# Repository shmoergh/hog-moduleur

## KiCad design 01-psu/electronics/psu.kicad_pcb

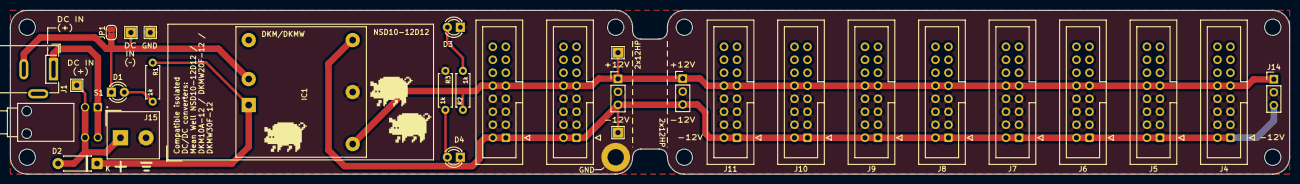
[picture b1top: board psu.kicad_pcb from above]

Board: 2 copper layers, 250.0 x 32.0 mm, 38 parts (0 on the bottom side), 10 nets.

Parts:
D1, D3, D4: LED; LED_D3.0mm
D2: 1N4001; D_DO-41_SOD81_P7.62mm_Horizontal
H1, H2, H3, H4, H5, H6, H7: MountingHole; MountingHole_3.2mm_M3_DIN965
H9: MountingHole_Pad; MountingHole_3.2mm_M3_DIN965_Pad
IC1: ISOLATED_DC-DC_CONV; Converter_DCDC_MeanWell_NSD10_DKMW_THT
J1: Barrel_Jack_Switch; BarrelJack_Wuerth_6941xx301002
J2, J3, J4, J5, J6, J7, J8, J9, J10, J11: Conn_02x08_Odd_Even; IDC-Header_2x08_P2.54mm_Vertical
J12, J13, J14: Conn_01x03; PinHeader_1x03_P2.54mm_Vertical
J15: Screw_Terminal_01x02; Altech_AK100_1x02_P5.00mm
JP1: Jumper_2_Open; SolderJumper-2_P1.3mm_Bridged2Bar_RoundedPad1.0x1.5mm
R1, R2, R3: 1k; R_Axial_DIN0207_L6.3mm_D2.5mm_P7.62mm_Horizontal
S1: PB400EEQR1BLK; SW_PB400EEQR1BLK
TP1, TP2, TP3, TP4, TP5: TestPoint; TestPoint_THTPad_2.0x2.0mm_Drill1.0mm

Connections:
+12V: IC1.3 (+OUT), J2.9, J2.10, J3.9, J3.10, J4.9, J4.10, J5.9, J5.10, J6.9, J6.10, J7.9, J7.10, J8.9, J8.10, J9.9, J9.10, J10.9, J10.10, J11.9, J11.10, J12.1, J13.1, J14.1, R2.1, TP4.1
-12V: D4.1 (K), IC1.5 (-OUT), J2.1, J2.2, J3.1, J3.2, J4.1, J4.2, J5.1, J5.2, J6.1, J6.2, J7.1, J7.2, J8.1, J8.2, J9.1, J9.2, J10.1, J10.2, J11.1, J11.2, J12.3, J13.3, J14.3, TP5.1
DC_IN_+: D2.1 (K), IC1.1 (+IN), R1.1
DC_IN_-: D1.1 (K), IC1.2 (-IN), J1.2, JP1.1 (A), TP2.1
GND: D3.1 (K), H9.1, IC1.4 (Common), J2.3, J2.4, J2.5, J2.6, J2.7, J2.8, J3.3, J3.4, J3.5, J3.6, J3.7, J3.8, J4.3, J4.4, J4.5, J4.6, J4.7, J4.8, J5.3, J5.4, J5.5, J5.6, J5.7, J5.8, J6.3, J6.4, J6.5, J6.6, J6.7, J6.8, J7.3, J7.4, J7.5, J7.6, J7.7, J7.8, J8.3, J8.4, J8.5, J8.6, J8.7, J8.8, J9.3, J9.4, J9.5, J9.6, J9.7, J9.8, J10.3, J10.4, J10.5, J10.6, J10.7, J10.8, J11.3, J11.4, J11.5, J11.6, J11.7, J11.8, J12.2, J13.2, J14.2, J15.2, JP1.2 (B), R3.1, TP3.1
unnamed: D1.2 (A), R1.2
unnamed: D2.2 (A), J15.1, S1.2, S1.4, TP1.1
unnamed: D3.2 (A), R2.2
unnamed: D4.2 (A), R3.2
unnamed: J1.1, S1.1, S1.3

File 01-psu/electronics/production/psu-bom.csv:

"Reference","Qty","Value","Part No.","Part URL","Vendor"
"D1,D3,D4","3","LED","604-WP710A10ID","https://mou.sr/45uKc0N","Mouser"
"D2","1","1N4001","637-1N4001 ","https://mou.sr/3DfEJyK","Mouser"
"IC1","1","ISOLATED_DC-DC_CONV","709-NSD10-12D12 ","https://mou.sr/3ZpECrS","Mouser"
"J1","1","Barrel_Jack_Switch","710-694106301002 ","https://mou.sr/4a9ckVQ","Mouser"
"J2,J3,J4,J5,J6,J7,J8,J9,J10,J11","10","Conn_02x08_Odd_Even","737-BHR-16-VUA","https://mou.sr/4jUmWfT","Mouser"
"J15","1","Screw_Terminal_01x02","737-EBBA-02-C-SS-BU ","https://mou.sr/4jUbpxn","Mouser"
"R1,R2,R3","3","1k","303-MF0W4FF1001A10 ","https://mou.sr/3ZzOD6G","Mouser"
"S1","1","PB400EEQR1BLK","612-PB400EEQR1BLK ","https://mou.sr/3TDv9tV","Mouser"

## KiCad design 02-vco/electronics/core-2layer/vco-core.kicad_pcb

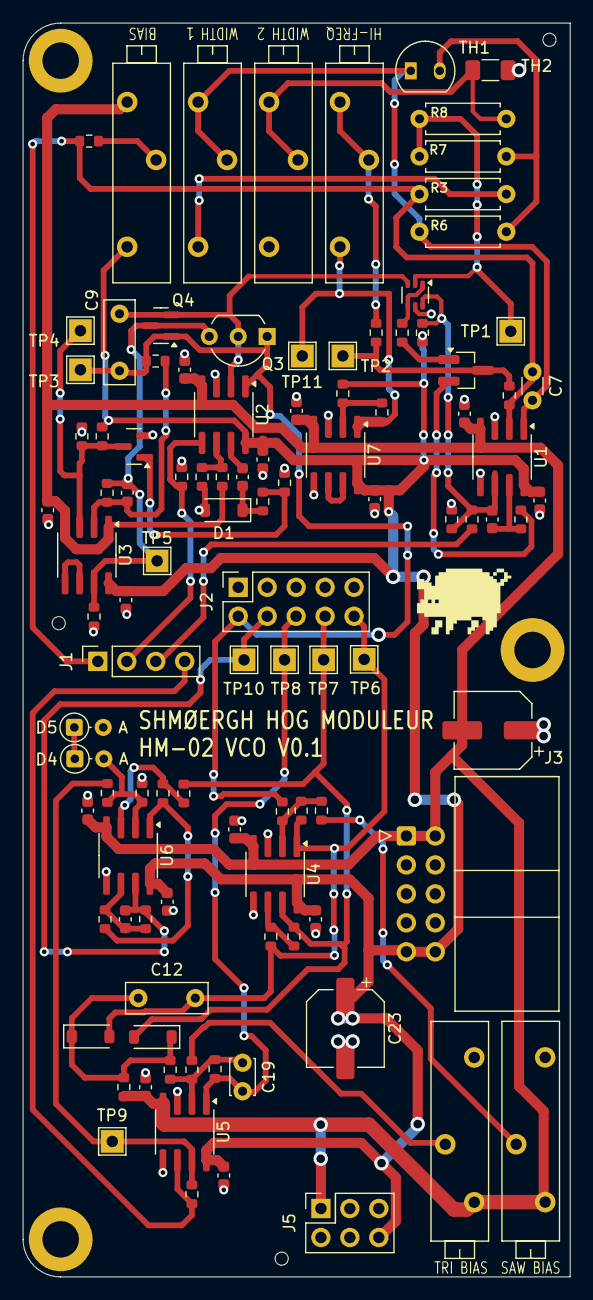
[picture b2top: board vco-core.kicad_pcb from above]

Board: 2 copper layers, 48.0 x 110.0 mm, 107 parts (0 on the bottom side), 49 nets.

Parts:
C1, C2, C3, C4, C5, C6, C13, C14, C15, C16, C17, C18, C21, C22: 100n; C_0603_1608Metric
C7: 100p-1n; C_Disc_D3.0mm_W1.6mm_P2.50mm
C8: 100p; C_0603_1608Metric
C9: 2.2nF (foil); C_Rect_L7.2mm_W2.5mm_P5.00mm_FKS2_FKP2_MKS2_MKP2
C10: 22p; C_0603_1608Metric
C11: 47p; C_0603_1608Metric
C12: 10p-100p; C_Rect_L7.0mm_W2.5mm_P5.00mm
C19: 22p; C_Disc_D3.0mm_W2.0mm_P2.50mm
C20: 33p; C_0603_1608Metric
C23, C24: 100u; CP_Elec_6.3x7.7
D1, D2, D3: 1N4148; D_SOD-123
D4, D5: 5.1V; D_DO-34_SOD68_P2.54mm_Vertical_AnodeUp
H1, H2, H3: MountingHole; MountingHole_3.2mm_M3_DIN965_Pad
J1: Conn_01x04; PinSocket_1x04_P2.54mm_Vertical
J2: Conn_02x05_Odd_Even; PinSocket_2x05_P2.54mm_Vertical
J3: Conn_02x05_Odd_Even; IDC-Header_2x05_P2.54mm_Horizontal
J5: Conn_02x03_Odd_Even; PinSocket_2x03_P2.54mm_Vertical
Q1: BC847BS; SOT-363_SC-70-6
Q2: MMBT3906; SOT-23_Handsoldering
Q3: J111; TO-92_Inline_Wide
Q4: MMBFJ111; SOT-23
Q5: MMBT5551; SOT-23
R1, R5, R15, R18, R21, R25, R27, R28, R29, R30, R37, R38, R40: 100k; R_0603_1608Metric
R2, R17: 150k; R_0603_1608Metric
R3, R6, R7, R8: See t.comp. table; R_Axial_DIN0207_L6.3mm_D2.5mm_P7.62mm_Horizontal
R4, R10, R13: 1M; R_0603_1608Metric
R9, R11: 1.5k; R_0603_1608Metric
R12: 510; R_0603_1608Metric
R14: 10k; R_0603_1608Metric
R16: 22k; R_0603_1608Metric
R19: 330k; R_0603_1608Metric
R20, R33: 2.2k; R_0603_1608Metric
R22, R32: 47k; R_0603_1608Metric
R23, R24: 15k; R_0603_1608Metric
R26: 27k; R_0603_1608Metric
R31, R34: 220k; R_0603_1608Metric
R35: 2.2M; R_0603_1608Metric
R36, R39: 240k; R_0603_1608Metric
RV_SAW_BIAS1: 10k; Potentiometer_Bourns_3006P_Horizontal
RV_TRI_BIAS1: 100k; Potentiometer_Bourns_3006P_Horizontal
R_BIAS1: 100k (prec); Potentiometer_Bourns_3006P_Horizontal
R_HIFREQ1: 2k (prec); Potentiometer_Bourns_3006P_Horizontal
R_WIDTH1, R_WIDTH2: See t.comp. table; Potentiometer_Bourns_3006P_Horizontal
TH1: See t.comp. table; TO-92-2
TH2: PTS120602B100RP100; R_1206_3216Metric_Pad1.30x1.75mm_HandSolder
TP1: -18mV/V; TestPoint_THTPad_2.0x2.0mm_Drill1.0mm
TP2: HiFreq; TestPoint_THTPad_2.0x2.0mm_Drill1.0mm
TP3: RAW_SAW; TestPoint_THTPad_2.0x2.0mm_Drill1.0mm
TP4: VCOVREF; TestPoint_THTPad_2.0x2.0mm_Drill1.0mm
TP5: Reset OUT; TestPoint_THTPad_2.0x2.0mm_Drill1.0mm
TP6: SAWInv; TestPoint_THTPad_2.0x2.0mm_Drill1.0mm
TP7: SAW; TestPoint_THTPad_2.0x2.0mm_Drill1.0mm
TP8: TRI; TestPoint_THTPad_2.0x2.0mm_Drill1.0mm
TP9: PW; TestPoint_THTPad_2.0x2.0mm_Drill1.0mm
TP10: SQR; TestPoint_THTPad_2.0x2.0mm_Drill1.0mm
TP11: -5V; TestPoint_THTPad_2.0x2.0mm_Drill1.0mm
U1, U2, U4, U5, U6, U7: TL072; SOIC-8_3.9x4.9mm_P1.27mm
U3: LM311; SOIC-8_3.9x4.9mm_P1.27mm

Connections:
+12V: C1.1, C3.1, C5.1, C13.1, C15.1, C17.1, C21.1, C23.1, J3.9, J3.10, J5.6, R10.1, R17.2, R39.1, R_BIAS1.1, U1.8 (V+), U2.8 (V+), U3.8 (V+), U4.8 (V+), U5.8 (V+), U6.8 (V+), U7.8 (V+)
-5V: R40.2, R_HIFREQ1.1, TP11.1, U7.1
-12V: C2.2, C4.2, C6.2, C14.2, C16.2, C18.2, C22.2, C24.2, J3.1, J3.2, J5.1, R15.2, R25.2, RV_SAW_BIAS1.3, RV_TRI_BIAS1.3, R_BIAS1.3, U1.4 (V-), U2.4 (V-), U3.1 (GND), U3.4 (V-), U4.4 (V-), U5.4 (V-), U6.4 (V-), U7.4 (V-)
/Raw oscillator/HI_FREQ_COMP: Q2.3 (C), R2.2, R12.1, TP2.1
/Raw oscillator/I_REF: C8.1, Q1.6 (C1), R4.2, R5.2, R10.2, U1.6 (-)
CV: C7.1, J1.1, R1.2, R2.1, R3.1, U1.2 (-)
FM: J1.3, R4.1
GND: C1.2, C2.1, C3.2, C4.1, C5.2, C6.1, C13.2, C14.1, C15.2, C16.1, C17.2, C18.1, C21.2, C22.1, C23.2, C24.1, D1.2 (A), D5.2 (A), J2.1, J2.3, J2.5, J2.7, J2.9, J3.3, J3.4, J3.5, J3.6, J3.7, J3.8, J5.2, J5.3, J5.4, J5.5, Q1.5 (B2), Q5.2 (E), R5.1, R13.2, R14.1, R18.1, R20.2, R22.2, R34.2, RV_SAW_BIAS1.1, RV_TRI_BIAS1.1, R_WIDTH2.1, TH2.2, U1.3 (+), U1.5 (+), U2.3 (+), U4.3 (+), U4.5 (+), U5.3 (+), U5.5 (+), U6.5 (+), U7.3 (+), U7.5 (+)
HARD_SYNC: J1.2, R13.1, U2.5 (+)
unnamed: C7.2, R6.1, R_WIDTH1.2, R_WIDTH1.3, TH1.1, U1.1
unnamed: C8.2, R9.1, U1.7
unnamed: C11.1, U2.7
unnamed: C11.2, D1.1 (K), R21.1
unnamed: C12.1, D2.1 (K), D3.1 (K), R25.1, R27.2
unnamed: D4.2 (A), R32.1, R34.1, U6.2 (-)
unnamed: D4.1 (K), D5.1 (K)
unnamed: Q1.2 (B1), R7.2, R8.1, TP1.1
unnamed: Q1.1 (E1), Q1.4 (E2), R11.1
unnamed: C9.1, Q1.3 (C2), Q3.2 (S), Q4.2 (S), U2.2 (-)
unnamed: Q2.2 (B), R9.2
unnamed: Q2.1 (E), R11.2
unnamed: C10.2, Q3.3 (G), Q4.3 (G), R19.2, R20.1, TP5.1, U3.7
unnamed: Q5.1 (B), R21.2, R22.1
unnamed: Q5.3 (C), R17.1, R18.2, TP4.1, U3.3 (-)
unnamed: R1.1, R_BIAS1.2
unnamed: R3.2, R_WIDTH1.1
unnamed: R6.2, R7.1, TH1.2
unnamed: R8.2, R_WIDTH2.2, R_WIDTH2.3, TH2.1
unnamed: R12.2, R_HIFREQ1.2, R_HIFREQ1.3
unnamed: R24.2, RV_SAW_BIAS1.2
unnamed: R28.2, RV_TRI_BIAS1.2
unnamed: R32.2, R37.2, TP9.1, U5.7
unnamed: R35.1, R36.2, U6.1
unnamed: R14.2, R15.1, U2.6 (-)
unnamed: C10.1, R16.2, R19.1, U3.2 (+)
unnamed: U3.5 (BAL), U3.6 (STRB)
unnamed: R23.1, R24.1, R26.2, U4.2 (-)
unnamed: R29.1, R30.2, U4.6 (-)
unnamed: C19.2, R27.1, R28.1, R31.2, U5.2 (-)
unnamed: R33.1, R35.2, U6.3 (+)
unnamed: C20.1, R36.1, R38.2, U6.6 (-)
unnamed: R39.2, R40.1, U7.2 (-)
unnamed: U7.6 (-), U7.7
RAW_SAW: C9.2, J2.2, Q3.1 (D), Q4.1 (D), R16.1, R23.2, TP3.1, U2.1
SAW: D2.2 (A), J2.8, R30.1, R33.2, TP7.1, U4.7
SAW_INV: C12.2, D3.2 (A), J2.10, R26.1, R29.2, TP6.1, U4.1
SQR: C20.2, J2.4, R38.1, TP10.1, U6.7
SQR_SHAPE: J1.4, R37.1, U5.6 (-)
TRI: C19.1, J2.6, R31.1, TP8.1, U5.1

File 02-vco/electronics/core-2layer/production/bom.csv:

Designator,Footprint,Quantity,Value,LCSC Part #
"_3, _2, ",,3,,
"C1, C13, C14, C15, C16, C17, C18, C2, C21, C22, C3, C4, C5, C6",0603,14,100n,C14663
C10,0603,1,22p,C1653
C11,0603,1,47p,C1671
C20,0603,1,33p,C1663
"C23, C24",CP_Elec_6.3x7.7,2,100u,C2836437
C8,0603,1,100p,C14858
"D1, D2, D3",D_SOD-123,3,1N4148,C81598
J1,PinSocket_1x04_P2.54mm_Vertical,1,Conn_01x04,
J2,PinSocket_2x05_P2.54mm_Vertical,1,Conn_02x05_Odd_Even,
J3,IDC-Header_2x05_P2.54mm_Horizontal,1,Conn_02x05_Odd_Even,
J5,PinSocket_2x03_P2.54mm_Vertical,1,Conn_02x03_Odd_Even,
Q1,SOT-363_SC-70-6,1,BC847BS,C5380687
Q2,SOT-23_Handsoldering,1,MMBT3906,C7420354
Q4,SOT-23,1,MMBFJ111,C274688
Q5,SOT-23,1,MMBT5551,C2145
"R1, R15, R18, R21, R25, R27, R28, R29, R30, R37, R38, R40, R5",0603,13,100k,C25803
"R10, R13, R4",0603,3,1M,C22935
"R11, R9",0603,2,1.5k,C22843
R12,0603,1,510,C23193
R14,0603,1,10k,C25804
R16,0603,1,22k,C31850
"R17, R2",0603,2,150k,C22807
R19,0603,1,330k,C23137
"R20, R33",0603,2,2.2k,C4190
"R22, R32",0603,2,47k,C25819
"R23, R24",0603,2,15k,C22809
R26,0603,1,27k,C22967
"R31, R34",0603,2,220k,C22961
R35,0603,1,2.2M,C22938
R36,0603,1,240k,C4197
R39,0603,1,240k,C2907016
RV_SAW_BIAS1,Potentiometer_Bourns_3006P_Horizontal,1,10k,
RV_TRI_BIAS1,Potentiometer_Bourns_3006P_Horizontal,1,100k,
"U1, U2, U4, U5, U6, U7",SOIC-8_3.9x4.9mm_P1.27mm,6,TL072,C6961
U3,SOIC-8_3.9x4.9mm_P1.27mm,1,LM311,C12597

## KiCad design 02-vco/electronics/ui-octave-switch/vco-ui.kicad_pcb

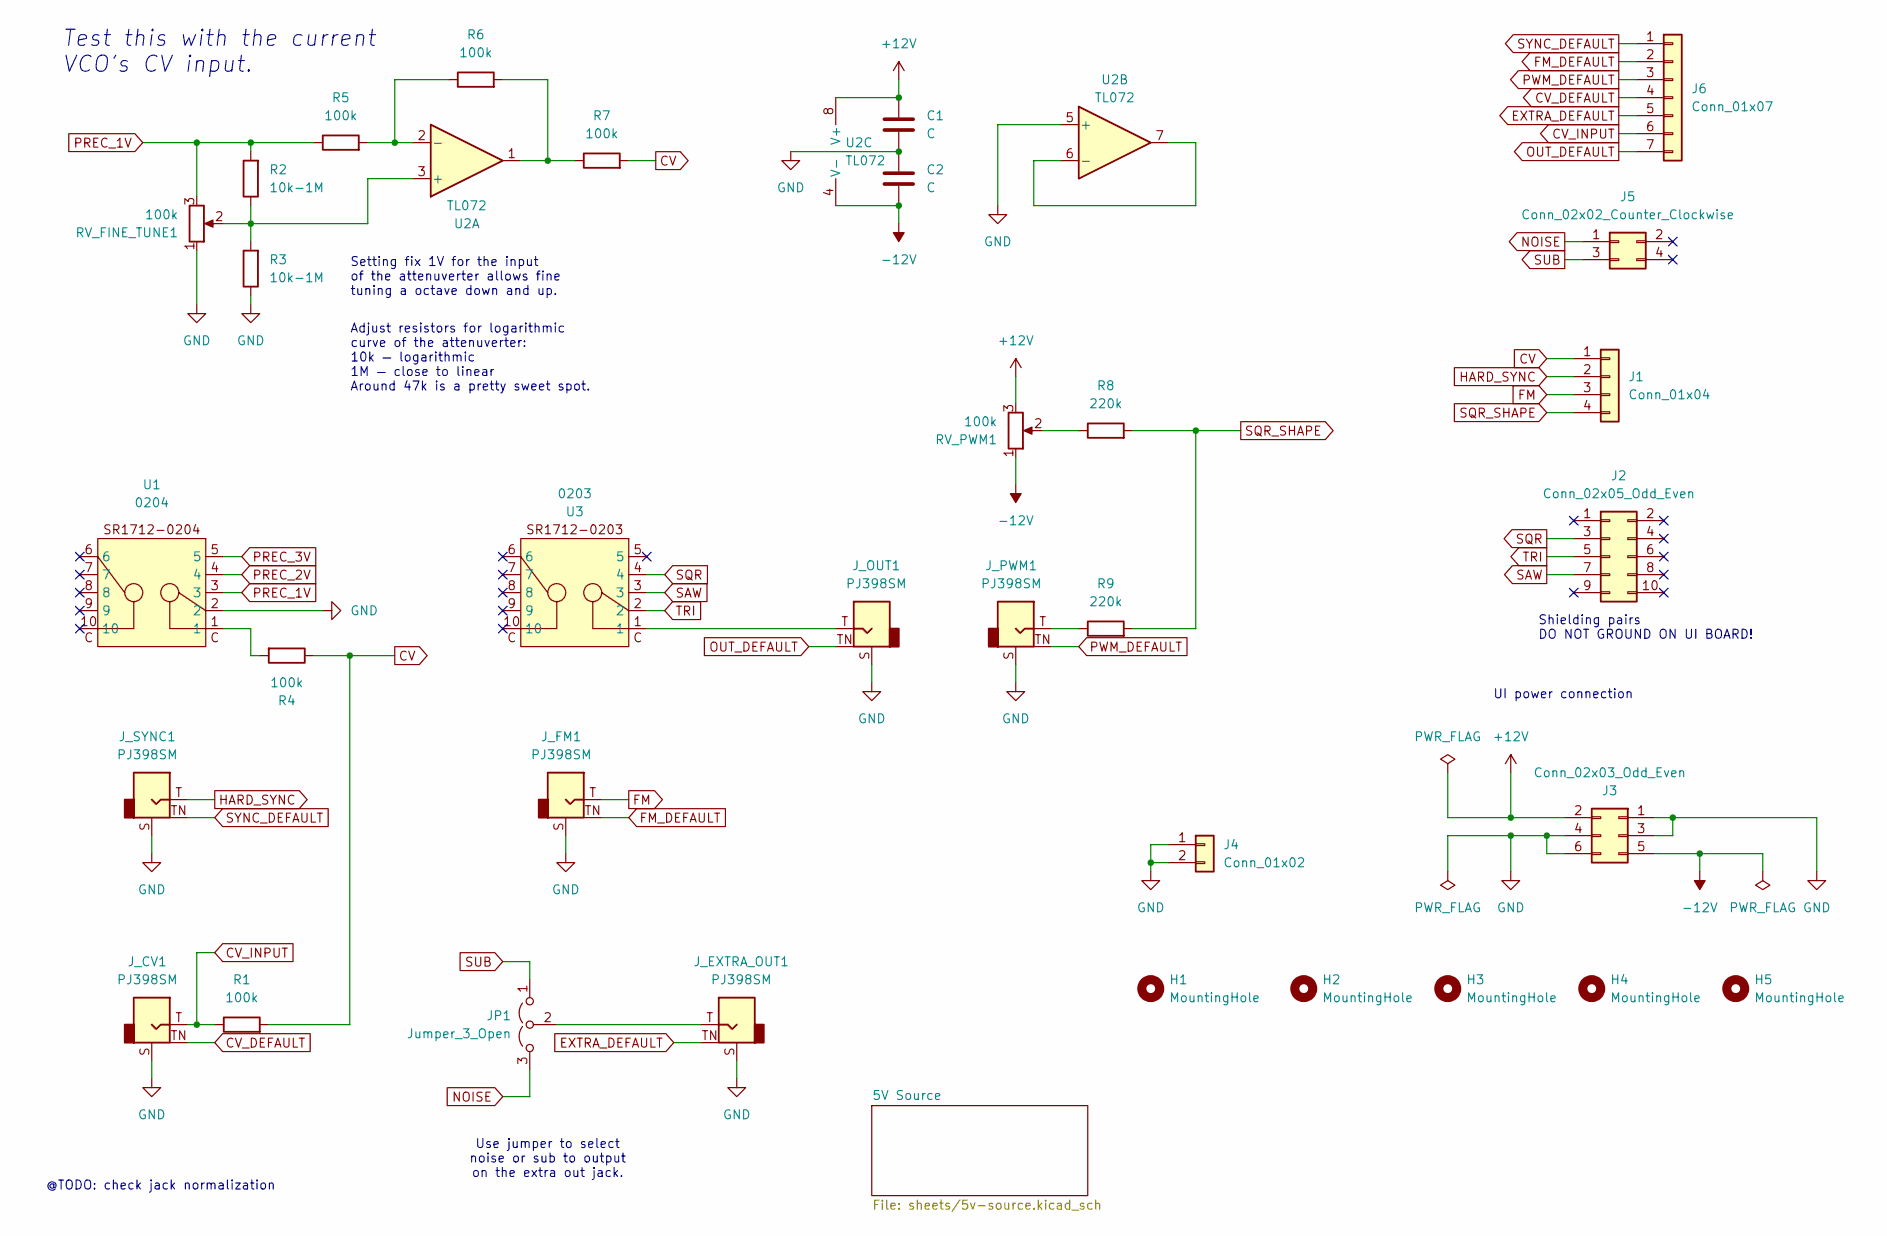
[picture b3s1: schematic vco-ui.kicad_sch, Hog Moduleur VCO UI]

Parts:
C1, C2: C; C_Disc_D5.0mm_W2.5mm_P2.50mm
H1, H2, H3, H4, H5: MountingHole; MountingHole_3.2mm_M3_DIN965_Pad
J1: Conn_01x04; PinSocket_1x04_P2.54mm_Vertical; Part no. 200-SSW10401TMS
J2: Conn_02x05_Odd_Even; PinSocket_2x05_P2.54mm_Vertical; Part no. 200-SSW10501TD
J3: Conn_02x03_Odd_Even; PinSocket_2x03_P2.54mm_Vertical; Part no. 200-SSW10301TD
J4: Conn_01x02; PinSocket_1x02_P2.54mm_Vertical; Part no. 200-SSW10201TS
J5: Conn_02x02_Counter_Clockwise; PinSocket_2x02_P2.54mm_Vertical; Part no. 200-SSW10206TD
J6: Conn_01x07; PinSocket_1x07_P2.54mm_Vertical; Part no. 200-SSW10601TS
JP1: Jumper_3_Open; PinHeader_1x03_P2.54mm_Horizontal; Part no. 200-HTSW10308TSRA
J_CV1: PJ398SM; Jack_3.5mm_QingPu_WQP-PJ398SM_Vertical_CircularHoles; Part no. PJ398SM
J_EXTRA_OUT1: PJ398SM; Jack_3.5mm_QingPu_WQP-PJ398SM_Vertical_CircularHoles; Part no. PJ398SM
J_FM1: PJ398SM; Jack_3.5mm_QingPu_WQP-PJ398SM_Vertical_CircularHoles; Part no. PJ398SM
J_OUT1: PJ398SM; Jack_3.5mm_QingPu_WQP-PJ398SM_Vertical_CircularHoles; Part no. PJ398SM
J_PWM1: PJ398SM; Jack_3.5mm_QingPu_WQP-PJ398SM_Vertical_CircularHoles; Part no. PJ398SM
J_SYNC1: PJ398SM; Jack_3.5mm_QingPu_WQP-PJ398SM_Vertical_CircularHoles; Part no. PJ398SM
R1, R4, R5, R6, R7: 100k; R_Axial_DIN0207_L6.3mm_D2.5mm_P7.62mm_Horizontal; Part no. 603-MFR-25FRF52100K
R2, R3: 10k-1M; R_Axial_DIN0207_L6.3mm_D2.5mm_P7.62mm_Horizontal; Part no. 603-MFR-25FRF52100K
R8, R9: 220k; R_Axial_DIN0207_L6.3mm_D2.5mm_P7.62mm_Horizontal; Part no. 603-MFR-25FRF52-220K
RV_FINE_TUNE1: 100k; Potentiometer_Bourns_Single-PTV09A; Part no. 652-PTV09A4025FB104
RV_PWM1: 100k; Potentiometer_Bourns_Single-PTV09A; Part no. 652-PTV09A4025FB104
U1: 0204; SR1712-0204
U2: TL072; DIP-8_W7.62mm_LongPads
U3: 0203; SR1712-0203; Part no. 105-SR1712F-23NS

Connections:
+12V: C1.1, J3.2, RV_PWM1.3, U2.8 (V+); also elsewhere on the board
-12V: C2.2, J3.5, RV_PWM1.1, U2.4 (V-)
CV: J1.1, R1.2, R4.1, R7.2
CV_DEFAULT: J6.4, J_CV1.TN
CV_INPUT: J6.6, J_CV1.T, R1.1
EXTRA_DEFAULT: J6.5, J_EXTRA_OUT1.TN
FM: J1.3, J_FM1.T
FM_DEFAULT: J6.2, J_FM1.TN
GND: C1.2, C2.1, J3.1, J3.3, J3.4, J3.6, J4.1, J4.2, J_CV1.S, J_EXTRA_OUT1.S, J_FM1.S, J_OUT1.S, J_PWM1.S, J_SYNC1.S, R3.1, RV_FINE_TUNE1.1, U1.2, U2.5 (+); also elsewhere on the board
HARD_SYNC: J1.2, J_SYNC1.T
NOISE: J5.1, JP1.3 (B)
unnamed: JP1.2 (C), J_EXTRA_OUT1.T
unnamed: J_OUT1.T, U3.1
unnamed: J_PWM1.T, R9.1
unnamed: R4.2, U1.1
unnamed: R6.2, R7.1, U2.1
unnamed: R8.1, RV_PWM1.2
unnamed: R2.1, R3.2, RV_FINE_TUNE1.2, U2.3 (+)
unnamed: R5.2, R6.1, U2.2 (-)
unnamed: U2.6 (-), U2.7
OUT_DEFAULT: J6.7, J_OUT1.TN
PREC_1V: R2.2, R5.1, RV_FINE_TUNE1.3, U1.3; also elsewhere on the board
PREC_2V: U1.4; also elsewhere on the board
PREC_3V: U1.5; also elsewhere on the board
PWM_DEFAULT: J6.3, J_PWM1.TN
SAW: J2.7, U3.3
SQR: J2.3, U3.4
SQR_SHAPE: J1.4, R8.2, R9.2
SUB: J5.3, JP1.1 (A)
SYNC_DEFAULT: J6.1, J_SYNC1.TN
TRI: J2.5, U3.2

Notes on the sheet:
Test this with the current VCO's CV input.
Setting fix 1V for the input of the attenuverter allows fine tuning a octave down and up.
@TODO: check jack normalization
UI power connection
Adjust resistors for logarithmic curve of the attenuverter: 10k — logarithmic 1M — close to linear Around 47k is a pretty sweet spot.
Use jumper to select noise or sub to output on the extra out jack.
Shielding pairs DO NOT GROUND ON UI BOARD!

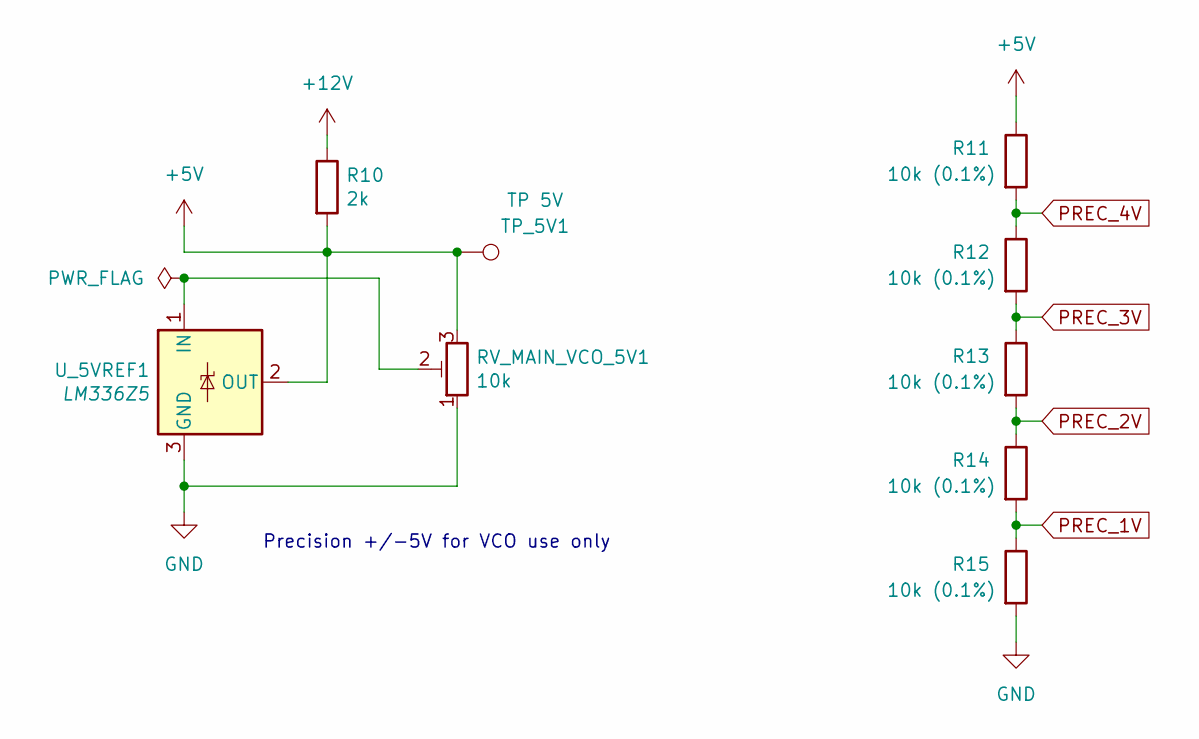
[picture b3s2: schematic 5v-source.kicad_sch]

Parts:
R10: 2k; R_Axial_DIN0207_L6.3mm_D2.5mm_P7.62mm_Horizontal; Part No. 603-MFR-25FTF52-2K
R11, R12, R13, R14, R15: 10k (0.1%); R_Axial_DIN0207_L6.3mm_D2.5mm_P7.62mm_Horizontal
RV_MAIN_VCO_5V1: 10k; Potentiometer_Bourns_3006P_Horizontal; Part No. 652-3006P-1-103-LF
TP_5V1: TP 5V; TestPoint_THTPad_2.0x2.0mm_Drill1.0mm
U_5VREF1: LM336Z5; TO-92L_Inline_Wide; Part No. 926-LM336Z-50/NOPB

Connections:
+5V: R10.2, R11.1, RV_MAIN_VCO_5V1.3, TP_5V1.1, U_5VREF1.2 (OUT)
+12V: R10.1; also elsewhere on the board
GND: R15.2, RV_MAIN_VCO_5V1.1, U_5VREF1.3 (GND); also elsewhere on the board
unnamed: RV_MAIN_VCO_5V1.2, U_5VREF1.1 (IN)
PREC_1V: R14.2, R15.1; also elsewhere on the board
PREC_2V: R13.2, R14.1; also elsewhere on the board
PREC_3V: R12.2, R13.1; also elsewhere on the board
PREC_4V: R11.2, R12.1

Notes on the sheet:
Precision +/-5V for VCO use only

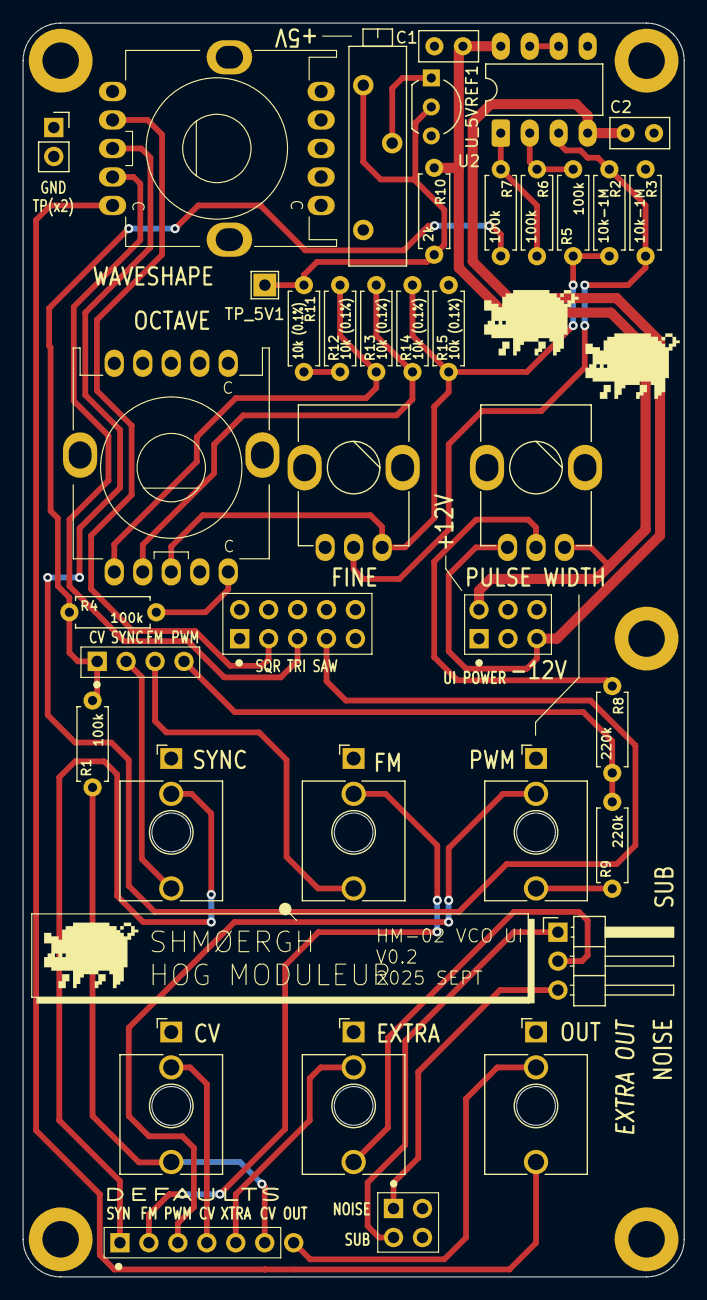
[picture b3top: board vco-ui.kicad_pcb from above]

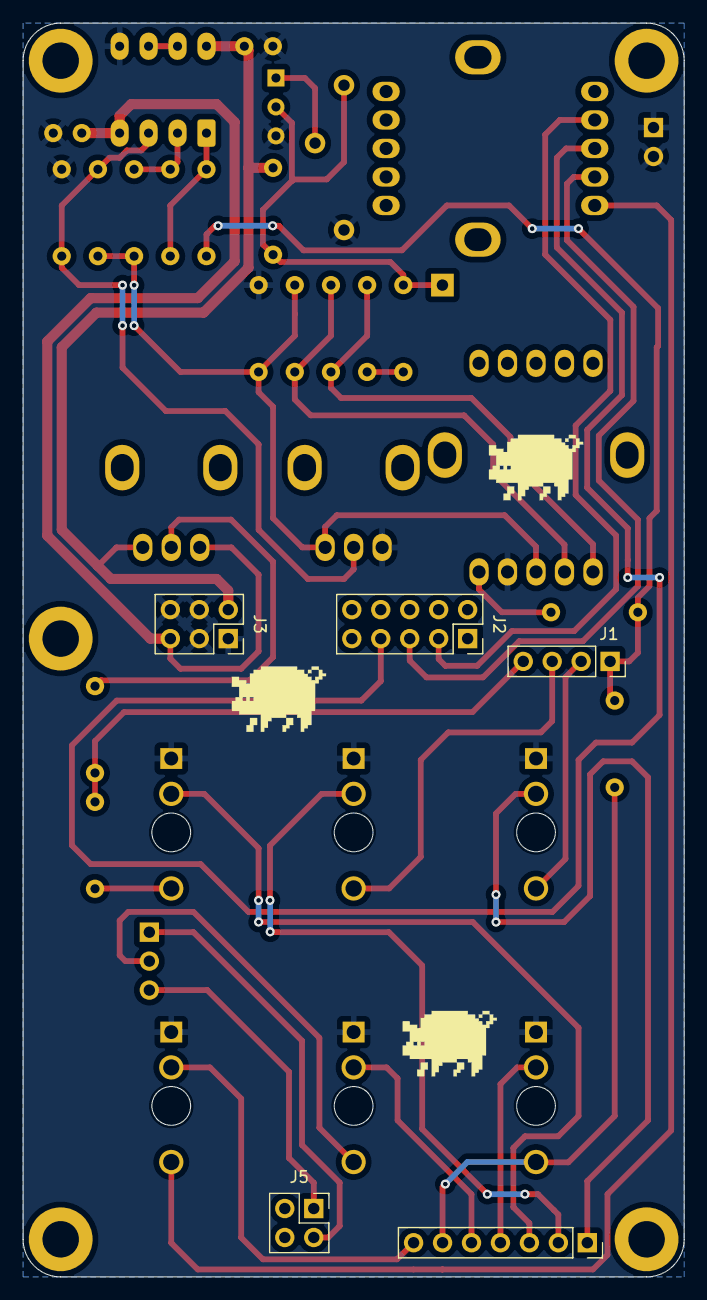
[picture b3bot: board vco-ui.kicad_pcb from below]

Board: 2 copper layers, 58.0 x 110.0 mm, 43 parts (5 on the bottom side), 34 nets.
